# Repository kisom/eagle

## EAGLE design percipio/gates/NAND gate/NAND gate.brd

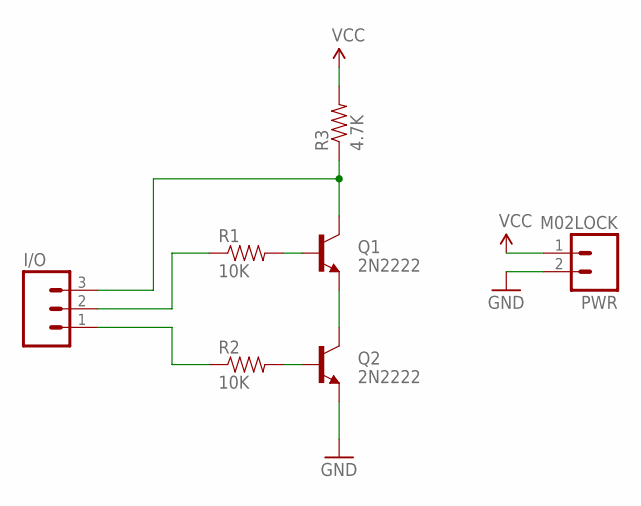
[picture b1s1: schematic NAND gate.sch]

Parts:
I/O: M03LOCK; 1X03_LOCK
PWR: M02LOCK; 1X02_LOCK
Q1, Q2: 2N2222; TO-92-AMMO
R1, R2: 10K; AXIAL-0.4
R3: 4.7K; AXIAL-0.4

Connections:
GND: PWR.2, Q2.1 (E)
unnamed: Q1.2 (B), R1.P$2 (2)
unnamed: Q2.2 (B), R2.P$2 (2)
unnamed: I/O.2, R1.P$1 (1)
unnamed: I/O.1, R2.P$1 (1)
unnamed: I/O.3, Q1.3 (C), R3.P$1 (1)
unnamed: Q1.1 (E), Q2.3 (C)
VCC: PWR.1, R3.P$2 (2)

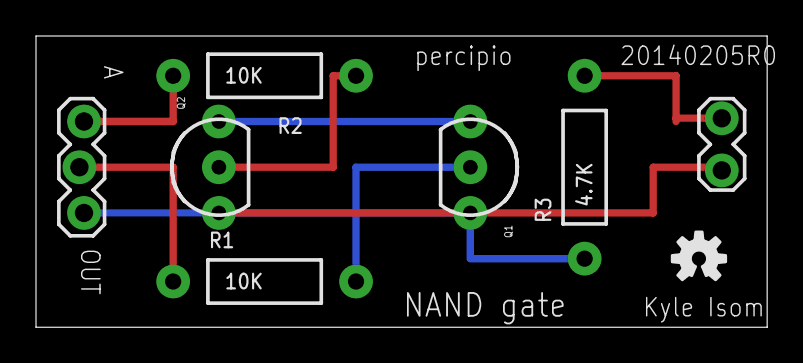
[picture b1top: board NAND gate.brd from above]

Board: 2 copper layers, 40.6 x 16.2 mm, 8 parts (0 on the bottom side), 8 nets.

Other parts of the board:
U$1: OSHW-LOGO-S

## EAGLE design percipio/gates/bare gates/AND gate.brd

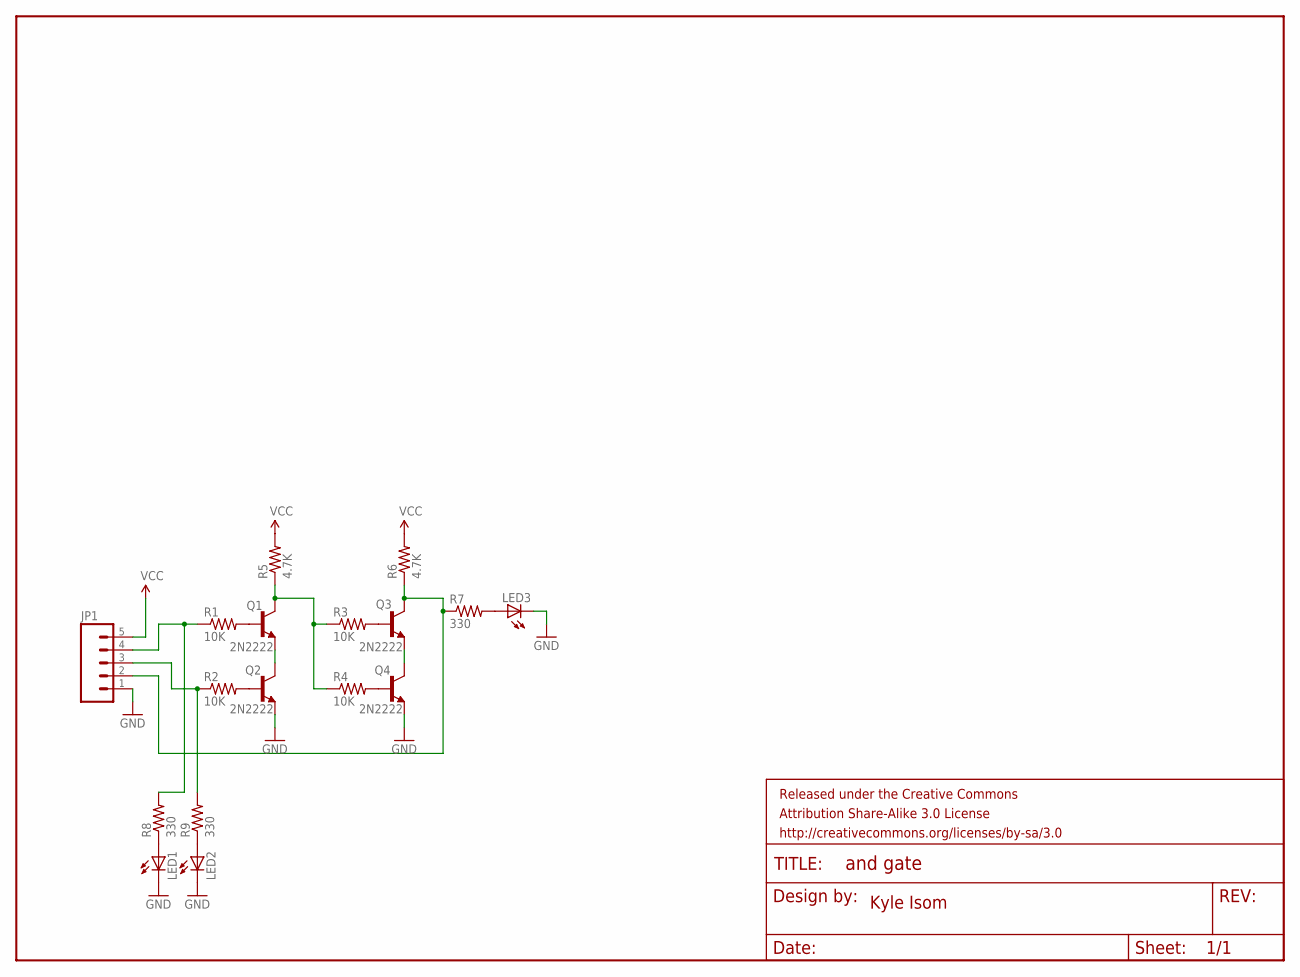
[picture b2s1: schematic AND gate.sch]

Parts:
FRAME1: FRAME-LETTER; CREATIVE_COMMONS
JP1: M05LOCK; 1X05_LOCK
LED1, LED2, LED3: LED3MM
Q1, Q2, Q3, Q4: 2N2222; TO-92-AMMO
R1, R2, R3, R4: 10K; AXIAL-0.4
R5, R6: 4.7K; AXIAL-0.4
R7, R8, R9: 330; AXIAL-0.4

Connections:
GND: JP1.1, LED1.K (C), LED2.K (C), LED3.K (C), Q2.1 (E), Q4.1 (E)
unnamed: Q1.2 (B), R1.P$2 (2)
unnamed: Q2.2 (B), R2.P$2 (2)
unnamed: Q3.2 (B), R3.P$2 (2)
unnamed: Q4.2 (B), R4.P$2 (2)
unnamed: JP1.2, Q3.3 (C), R6.P$1 (1), R7.P$1 (1)
unnamed: JP1.4, R1.P$1 (1), R8.P$2 (2)
unnamed: JP1.3, R2.P$1 (1), R9.P$2 (2)
unnamed: Q1.3 (C), R3.P$1 (1), R4.P$1 (1), R5.P$1 (1)
unnamed: Q1.1 (E), Q2.3 (C)
unnamed: Q3.1 (E), Q4.3 (C)
unnamed: LED3.A, R7.P$2 (2)
unnamed: LED1.A, R8.P$1 (1)
unnamed: LED2.A, R9.P$1 (1)
VCC: JP1.5, R5.P$2 (2), R6.P$2 (2)

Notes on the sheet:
Kyle Isom

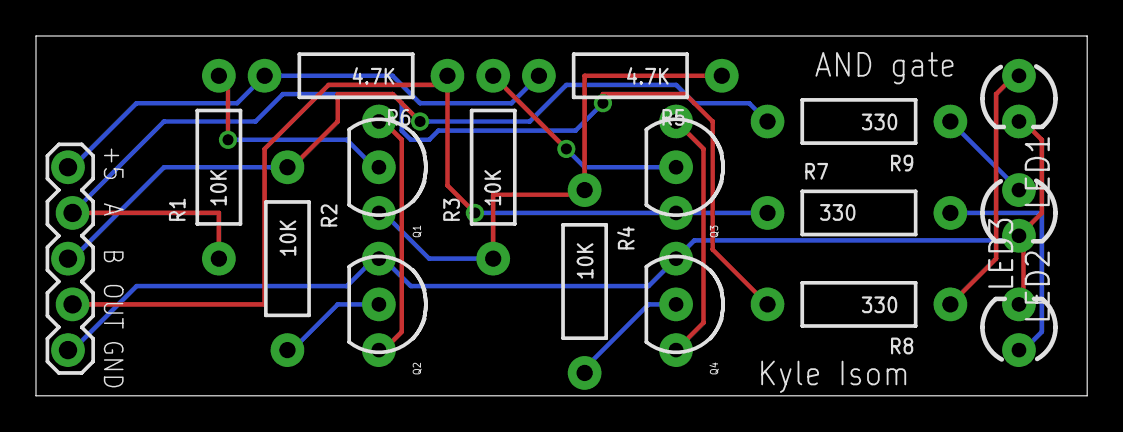
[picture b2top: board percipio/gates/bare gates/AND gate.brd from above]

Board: 2 copper layers, 58.4 x 20.0 mm, 18 parts (0 on the bottom side), 15 nets.

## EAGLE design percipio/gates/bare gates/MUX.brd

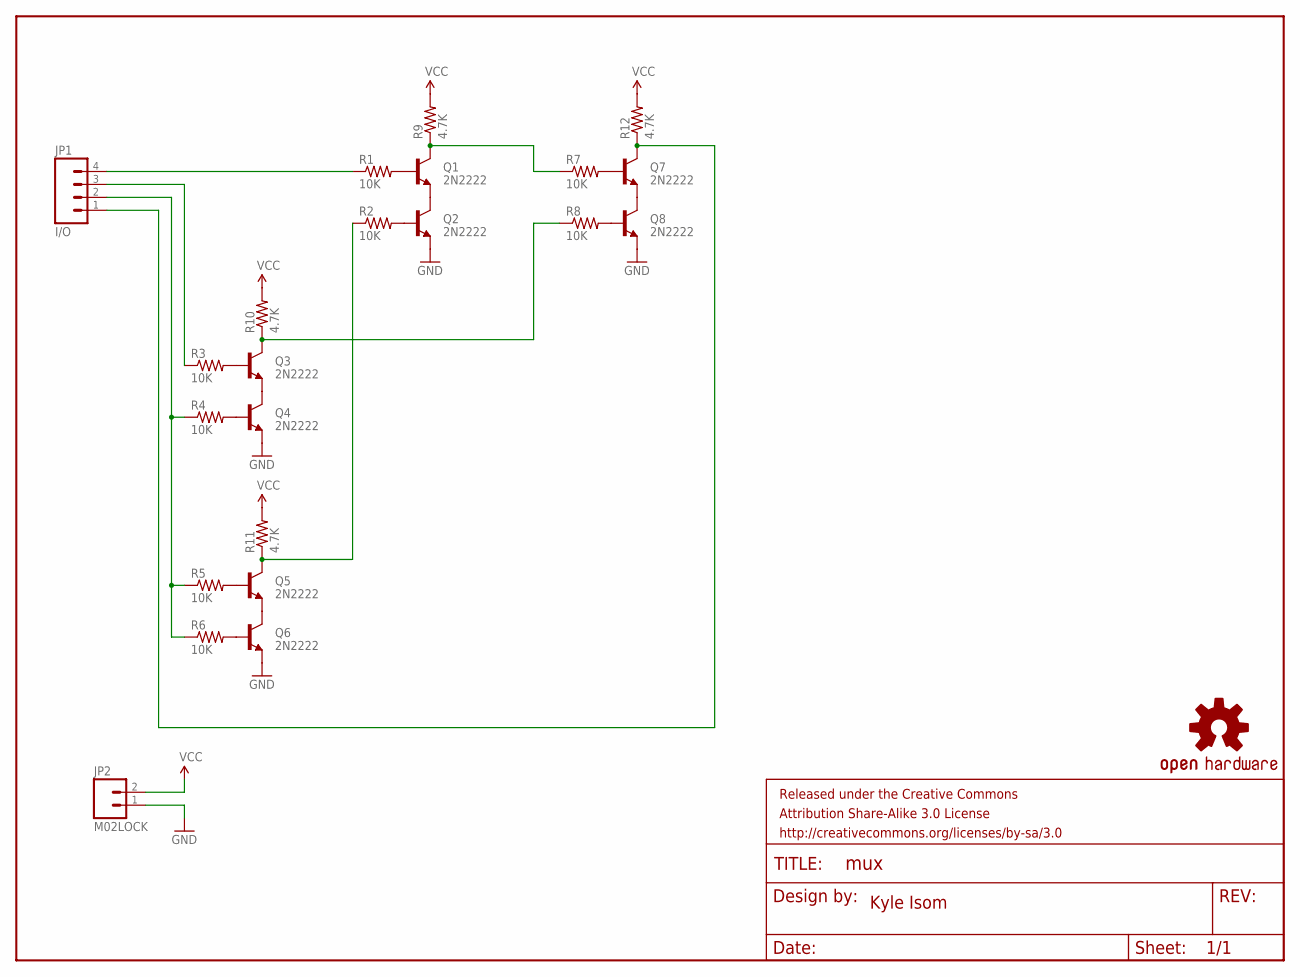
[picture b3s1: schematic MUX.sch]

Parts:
FRAME1: FRAME-LETTER; CREATIVE_COMMONS
JP1: I/O; 1X04_LOCK
JP2: M02LOCK; 1X02_LOCK
LOGO1: OSHW-LOGOS; OSHW-LOGO-S
Q1, Q2, Q3, Q4, Q5, Q6, Q7, Q8: 2N2222; TO-92-AMMO
R1, R2, R3, R4, R5, R6, R7, R8: 10K; AXIAL-0.4
R9, R10, R11, R12: 4.7K; AXIAL-0.4

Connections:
GND: JP2.1, Q2.1 (E), Q4.1 (E), Q6.1 (E), Q8.1 (E)
unnamed: Q1.1 (E), Q2.3 (C)
unnamed: Q3.1 (E), Q4.3 (C)
unnamed: Q5.1 (E), Q6.3 (C)
unnamed: Q1.2 (B), R1.P$2 (2)
unnamed: Q2.2 (B), R2.P$2 (2)
unnamed: Q3.2 (B), R3.P$2 (2)
unnamed: Q4.2 (B), R4.P$2 (2)
unnamed: Q5.2 (B), R5.P$2 (2)
unnamed: Q6.2 (B), R6.P$2 (2)
unnamed: Q7.1 (E), Q8.3 (C)
unnamed: Q7.2 (B), R7.P$2 (2)
unnamed: Q8.2 (B), R8.P$2 (2)
unnamed: Q1.3 (C), R7.P$1 (1), R9.P$1 (1)
unnamed: Q3.3 (C), R8.P$1 (1), R10.P$1 (1)
unnamed: Q5.3 (C), R2.P$1 (1), R11.P$1 (1)
unnamed: JP1.1, Q7.3 (C), R12.P$1 (1)
unnamed: JP1.4, R1.P$1 (1)
unnamed: JP1.3, R3.P$1 (1)
unnamed: JP1.2, R4.P$1 (1), R5.P$1 (1), R6.P$1 (1)
VCC: JP2.2, R9.P$2 (2), R10.P$2 (2), R11.P$2 (2), R12.P$2 (2)

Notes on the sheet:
Kyle Isom

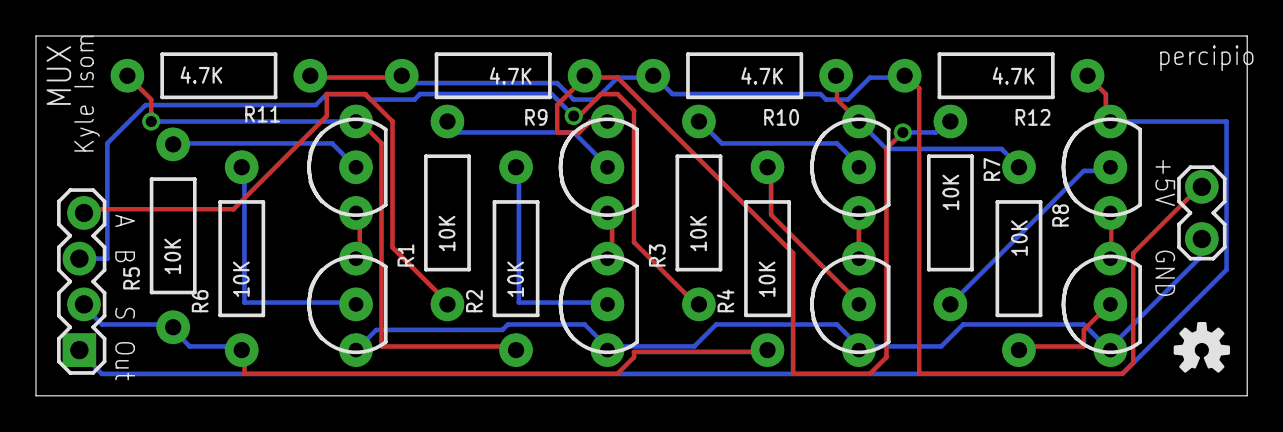
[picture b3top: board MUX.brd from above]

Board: 2 copper layers, 67.3 x 20.0 mm, 24 parts (0 on the bottom side), 21 nets.

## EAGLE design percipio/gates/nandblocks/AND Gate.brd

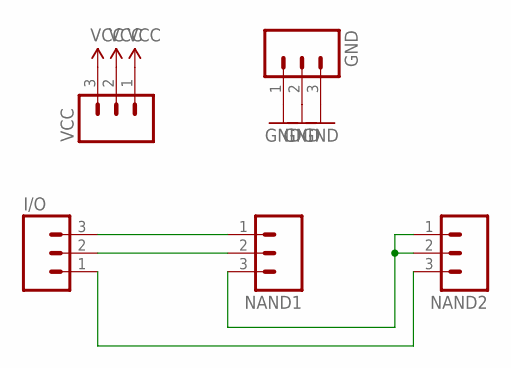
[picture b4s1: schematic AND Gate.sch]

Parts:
GND: M03LOCK; 1X03_LOCK
I/O: M03LOCK; 1X03_LOCK
NAND1, NAND2: M03LOCK; 1X03_LOCK
VCC: M03LOCK; 1X03_LOCK

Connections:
GND: GND.1, GND.2, GND.3
unnamed: I/O.1, NAND2.3
unnamed: NAND1.3, NAND2.1, NAND2.2
unnamed: I/O.3, NAND1.1
unnamed: I/O.2, NAND1.2
VCC: VCC.1, VCC.2, VCC.3

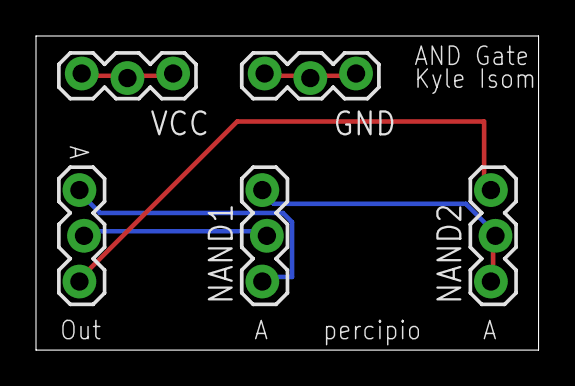
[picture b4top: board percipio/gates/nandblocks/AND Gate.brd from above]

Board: 2 copper layers, 27.9 x 17.4 mm, 5 parts (0 on the bottom side), 6 nets.

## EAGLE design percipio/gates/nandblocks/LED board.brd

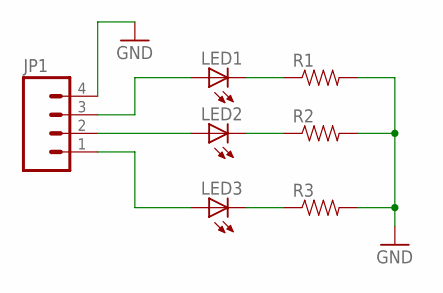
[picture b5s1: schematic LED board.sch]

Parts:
JP1: M04LOCK; 1X04_LOCK
LED1, LED2, LED3: LED3MM
R1, R2, R3: RESISTORPTH-1/6W; 1/6W-RES

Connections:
GND: JP1.4, R1.2, R2.2, R3.2
unnamed: JP1.3, LED1.A
unnamed: JP1.2, LED2.A
unnamed: JP1.1, LED3.A
unnamed: LED1.K (C), R1.1
unnamed: LED2.K (C), R2.1
unnamed: LED3.K (C), R3.1

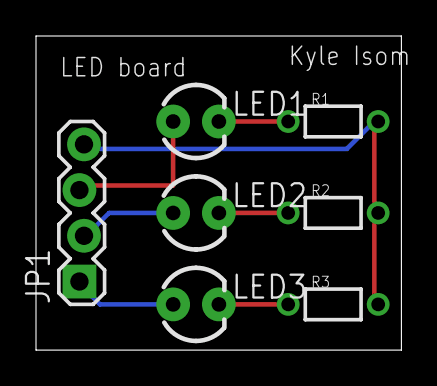
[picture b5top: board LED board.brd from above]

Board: 2 copper layers, 20.3 x 17.4 mm, 7 parts (0 on the bottom side), 7 nets.

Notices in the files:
parts and their libraries:
SparkFun-Connectors: Licensing: CC v3.0 Share-Alike You are welcome to use this library for commercial purposes.
SparkFun-Aesthetics: Released under the Creative Commons Attribution Share-Alike 3.0 License
SparkFun-Aesthetics: http://creativecommons.org/licenses/by-sa/3.0
